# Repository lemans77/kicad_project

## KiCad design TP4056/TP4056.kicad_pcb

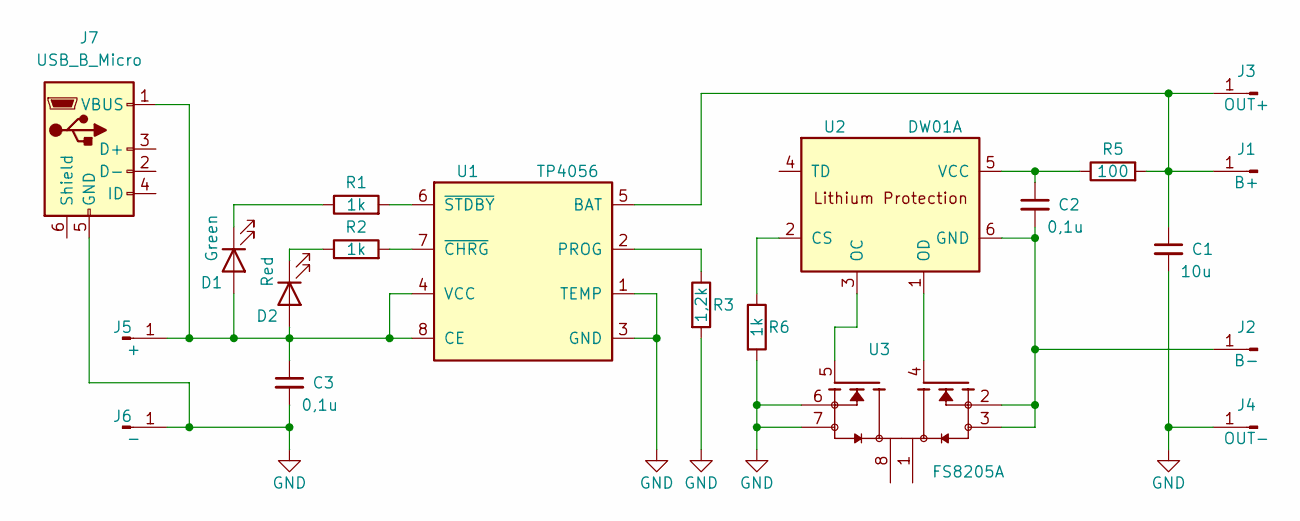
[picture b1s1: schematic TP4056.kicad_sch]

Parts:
C1: 10u; C_0603_1608Metric
C2, C3: 0,1u; C_0603_1608Metric
D1: Green; LED_0603_1608Metric
D2: Red; LED_0603_1608Metric
J1: B+; SolderWire-0.25sqmm_1x01_D0.65mm_OD1.7mm
J2: B-; SolderWire-0.25sqmm_1x01_D0.65mm_OD1.7mm
J3: OUT+; SolderWire-0.25sqmm_1x01_D0.65mm_OD1.7mm
J4: OUT-; SolderWire-0.25sqmm_1x01_D0.65mm_OD1.7mm
J5: +; SolderWire-0.25sqmm_1x01_D0.65mm_OD1.7mm
J6: -; SolderWire-0.25sqmm_1x01_D0.65mm_OD1.7mm
J7: USB_B_Micro; USB_Micro-B_Molex_47346-0001
R1, R2, R6: 1k; R_0603_1608Metric
R3: 1,2k; R_0603_1608Metric
R5: 100; R_0603_1608Metric
U1: TP4056; SOP127P600X175-9N
U2: DW01A; SOT23-6
U3: FS8205A; SOP65P640X120-8N

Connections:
GND: C1.2, C3.2, J4.1, J6.1, J7.5 (GND), R3.2, R6.2, U1.1 (TEMP), U1.3 (GND), U3.6, U3.7
unnamed: C3.1, D1.2 (A), D2.2 (A), J5.1, J7.1 (VBUS), U1.4 (VCC), U1.8 (CE)
unnamed: D1.1 (K), R1.1
unnamed: D2.1 (K), R2.1
unnamed: C1.1, J1.1, J3.1, R5.2, U1.5 (BAT)
unnamed: C2.2, J2.1, U2.6 (GND), U3.2, U3.3
unnamed: R3.1, U1.2 (PROG)
unnamed: R2.2, U1.7 (~CHRG)
unnamed: R1.2, U1.6 (~STDBY)
unnamed: R6.1, U2.2 (CS)
unnamed: U2.3 (OC), U3.5
unnamed: U2.1 (OD), U3.4
unnamed: C2.1, R5.1, U2.5 (VCC)

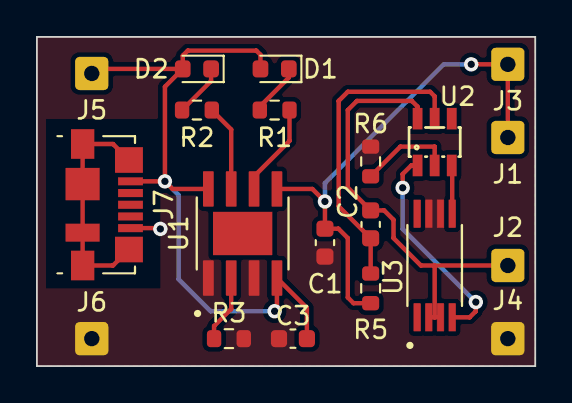
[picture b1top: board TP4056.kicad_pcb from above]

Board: 2 copper layers, 27.7 x 18.3 mm, 20 parts (0 on the bottom side), 13 nets.

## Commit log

2024-03-04 add project TP4056
